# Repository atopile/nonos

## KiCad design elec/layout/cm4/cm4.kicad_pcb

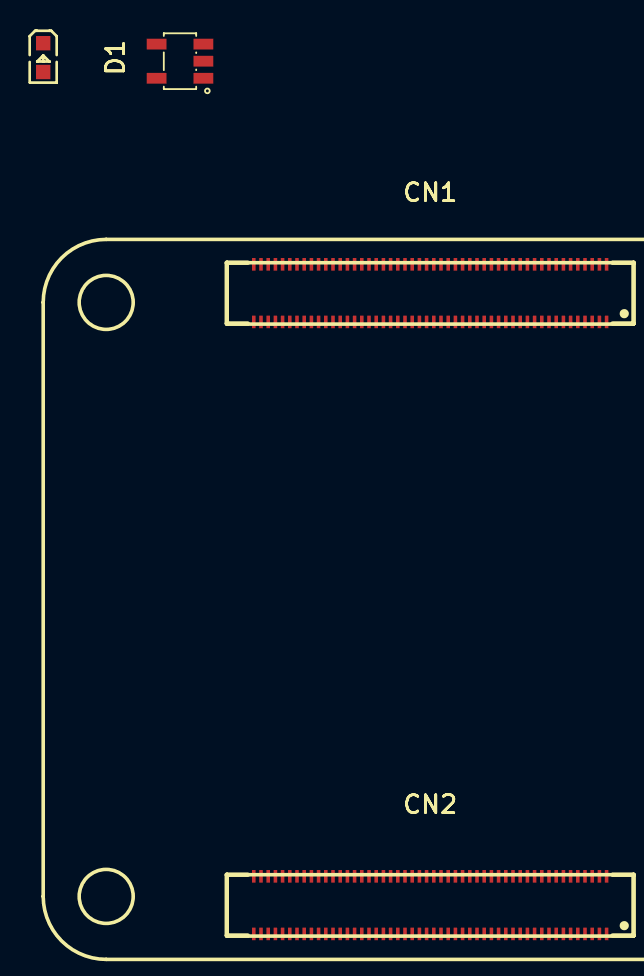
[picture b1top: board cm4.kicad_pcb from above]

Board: 2 copper layers, 4 parts (0 on the bottom side), 6 nets, no tracks yet.

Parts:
CN1, CN2: HRSHirose_DF40C_100DS_0_4V51; CONN-SMD_DF40C-100DS-0.4V-51
D1: 2.7V; LED0603-RD_WHITE
U1: _Texas_Instruments_SN74LVC1G07DBVR; SOT-23-5_L3.0-W1.7-P0.95-LS2.8-BR

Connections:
GND: CN1.1, CN1.4, CN1.7, CN1.11, CN1.16, CN1.21, CN1.26, CN1.30, CN1.33, CN1.37, CN1.49, CN1.65, CN1.68, CN1.71, CN1.74, CN1.79, CN1.84, CN1.89, CN1.90, CN1.94, CN1.97, CN1.100, CN2.4, CN2.7, CN2.10, CN2.13, CN2.16, CN2.19, CN2.22, CN2.28, CN2.31, CN2.34, CN2.37, CN2.40, CN2.43, CN2.46, CN2.49, CN2.52, CN2.55, CN2.58, CN2.61, CN2.64, CN2.67, CN2.70, CN2.73, CN2.82, CN2.85, CN2.88, CN2.91, CN2.94, CN2.97
PWR_LED: CN1.48, U1.2
VCC_1V8: CN1.44, CN1.45
VCC_3V3: CN1.39, CN1.42, CN1.43, D1.2, U1.5
VCC_5V: CN1.57, CN1.58, CN1.59, CN1.60, CN1.61, CN1.62
net: D1.1, U1.4

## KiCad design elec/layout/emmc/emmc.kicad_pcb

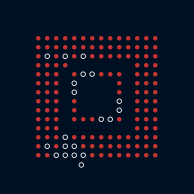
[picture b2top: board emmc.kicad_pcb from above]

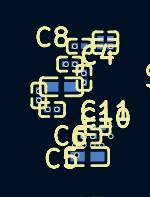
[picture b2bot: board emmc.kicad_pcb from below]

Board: 2 copper layers, 12 parts (11 on the bottom side), 5 nets, no tracks yet.

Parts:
C1: 10µF ±20% 6.3V X5R; C0402
C2, C3, C4, C6, C7, C8, C9, C11: 220nF ±20% 6.3V X5R; C0201
C5: 4.7µF ±20% 10V X5R; C0402
C10: 1µF ±20% 6.3V X5R; C0201
U1: _Samsung_KLMBG2JETD_B041; FBGA-153_L13.0-W11.5-P0.50_KLMAG1JETD-B041

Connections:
*6198-net: C5.1, C6.1, C7.1, C8.1, C9.1, U1.E6, U1.F5, U1.J10, U1.K9
*6198.eMMC.VDD_INTERNAL-net: C10.2, C11.2
VDD_INTERNAL: C10.1, C11.1, U1.C2
hv: C1.1, C2.1, C3.1, C4.1, U1.C6, U1.M4, U1.N4, U1.P3, U1.P5
lv: C1.2, C2.2, C3.2, C4.2, C5.2, C6.2, C7.2, C8.2, C9.2, U1.A6, U1.C4, U1.E7, U1.G5, U1.H10, U1.J5, U1.K8, U1.N2, U1.N5, U1.P4, U1.P6

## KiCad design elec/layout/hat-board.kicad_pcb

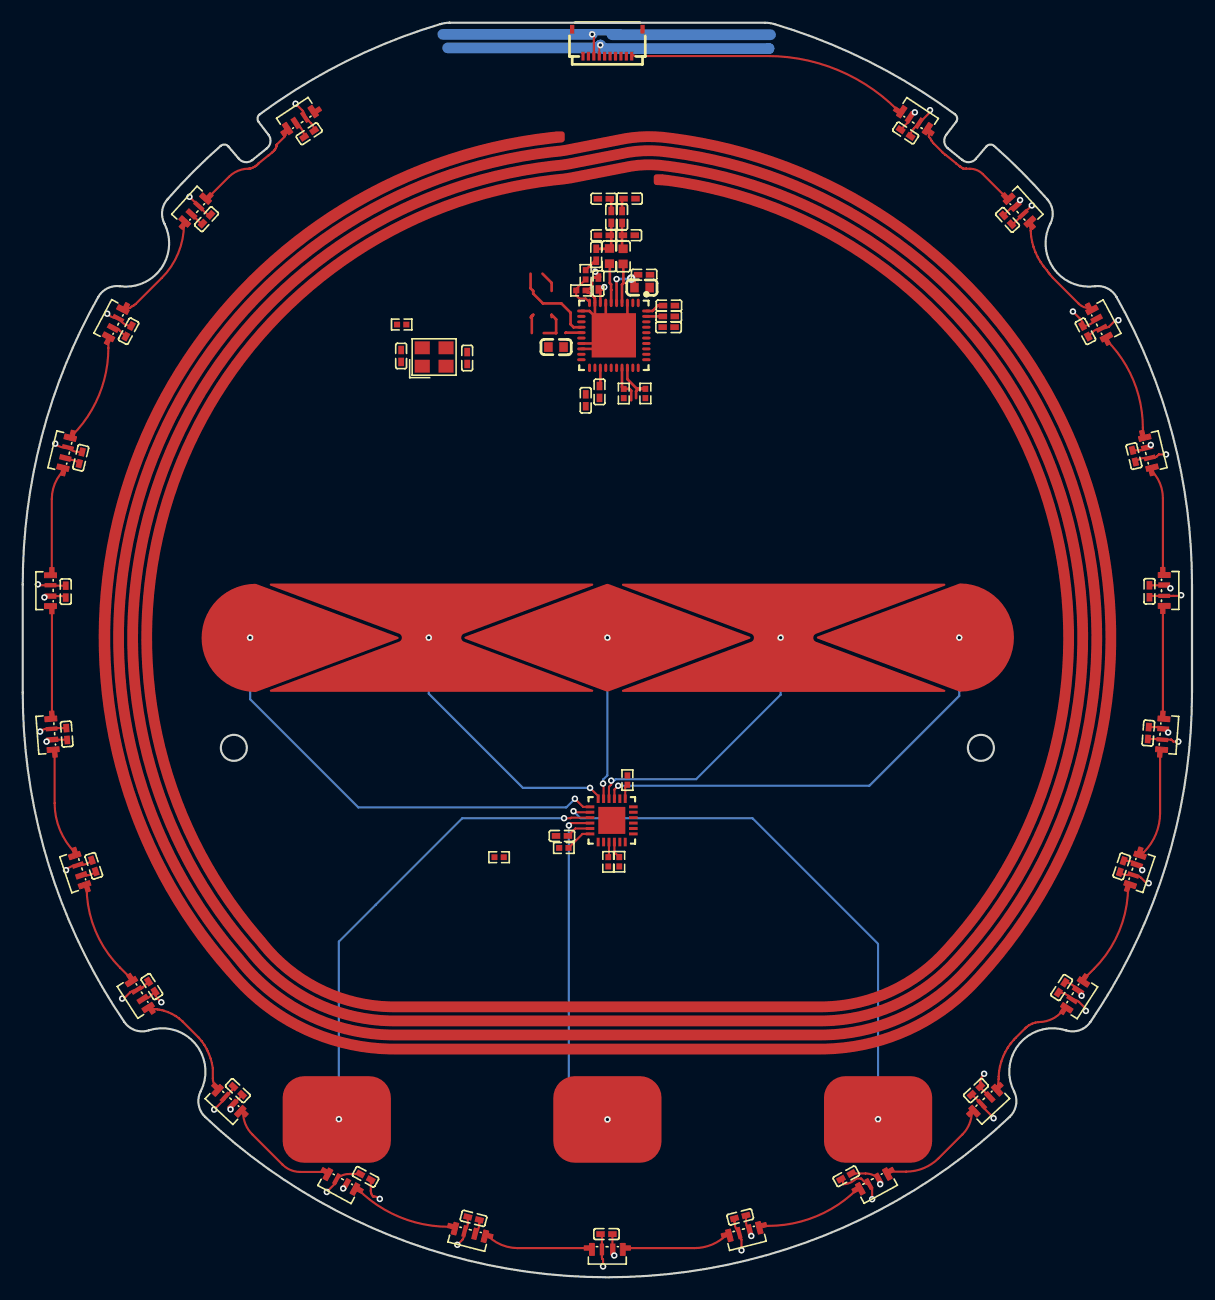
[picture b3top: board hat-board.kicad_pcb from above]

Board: 2 copper layers, 108.0 x 115.9 mm, 82 parts (0 on the bottom side), 60 nets.

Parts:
C1, C2, C14, C16: 20pF ±5% 50V C0G; C0402
C3, C5, C6, C7, C9, C10, C11, C12, C17, C18, C19, C20, C21, C22, C23, C24, C25, C26, C27, C28, C29, C30, C31, C32, C33, C34, C35, C36, C37, C38, C39, C42: 100nF ±10% 16V X7R; C0402
C4, C8: 10µF ±10% 10V X5R; C0603
C13, C15: 100pF ±5% 50V C0G; C0402
C40, C41: 220pF ±10% 50V X7R; C0402
FPC1: TE_Connectivity_1_2328702_0; FPC-SMD_10P-P0.50_HDGC_0.5K-HX-10PWB
L1, L2: 560nH ±5% 450mA 480mΩ; IND-SMD_L1.6-W0.8-1
P1: HatButtonAntenna; hat-button-antenna
R1, R2, R3, R5, R7, R8: 5.1kΩ ±1% 62.5mW; R0402
R4: 1kΩ ±1% 62.5mW; R0402
R6, R9, R10: 10kΩ ±1% 62.5mW; R0402
U1: _NXP_Semicon_PN5321A3HN_C106_51; QFN-40_L6.0-W6.0-P0.50-BL-EP4.1
U2, U3, U4, U5, U6, U7, U8, U9, U10, U11, U12, U13, U14, U15, U16, U17, U18, U19, U20, U21, U22, U23, U24: _OPSCO_Optoelectronics_SK6805SIDE_G_001; LED-SMD_4P-L3.5-W1.6_SK6805SIDE-G-001
U25: _Microchip_Tech_CAP1188_1_CP_TR; QFN-24_L4.0-W4.0-P0.50-TL-EP2.5
XTAL1: Crystal; CRYSTAL-SMD_4P-L3.2-W2.5-BL

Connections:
antenna_n: C15.1, C16.2, P1.9
antenna_p: C13.1, C14.2, P1.10
capacitive_sensor-net: R7.1, U25.4
capacitive_sensor-net-1: R8.1, U25.3
capacitive_sensor-net-2: R10.1, U25.24
capacitive_sensor-net-3: C42.2, U25.25
capacitive_sensor-net-4: C42.1, U25.23
capacitive_sensor.i2c-hv: R7.2, R8.2
gnd: C1.2, C2.2, C3.2, C4.2, C5.2, C6.2, C8.2, C9.2, C10.2, C11.1, C13.2, C15.2, C40.2, C41.2, FPC1.6, R5.1, U1.1, U1.3, U1.7, U1.9, U1.11, U1.17, U1.18, U1.41, XTAL1.2, XTAL1.4
hv: R1.2, R2.2
i2c_scl: FPC1.2, R1.1, U1.28
i2c_sda: FPC1.1, R2.1, U1.27
led_data: FPC1.10, U2.4
lv: C17.2, C18.2, C19.2, C20.2, C21.2, C22.2, C23.2, C24.2, C25.2, C26.2, C27.2, C28.2, C29.2, C30.2, C31.2, C32.2, C33.2, C34.2, C35.2, C36.2, C37.2, C38.2, C39.2, FPC1.3, U2.2, U3.2, U4.2, U5.2, U6.2, U7.2, U8.2, U9.2, U10.2, U11.2, U12.2, U13.2, U14.2, U15.2, U16.2, U17.2, U18.2, U19.2, U20.2, U21.2, U22.2, U23.2, U24.2
next_button: P1.3, U25.20
nfc-net: C12.2, R4.1
nfc-net-1: L1.2, U1.4
nfc-net-2: R4.2, R5.2, U1.10
nfc-net-3: R3.2, U1.15
nfc-net-4: C7.1, U1.37
nfc-net-5: C2.1, U1.14, XTAL1.3
nfc-net-6: L2.2, U1.6
nfc.nfc_ic-net: U1.20, U1.21, U1.22
nfc.oscillator-net: C1.1, R3.1, XTAL1.1
nfc_irq: FPC1.8, U1.25
play_button: P1.2, U25.22
power_3v3: C3.1, C4.1, C5.1, C6.1, C8.1, C9.1, C10.1, FPC1.5, U1.5, U1.8, U1.16, U1.23, U1.39, U1.40
power_5v: C17.1, C18.1, C19.1, C20.1, C21.1, C22.1, C23.1, C24.1, C25.1, C26.1, C27.1, C28.1, C29.1, C30.1, C31.1, C32.1, C33.1, C34.1, C35.1, C36.1, C37.1, C38.1, C39.1, FPC1.4, U2.3, U3.3, U4.3, U5.3, U6.3, U7.3, U8.3, U9.3, U10.3, U11.3, U12.3, U13.3, U14.3, U15.3, U16.3, U17.3, U18.3, U19.3, U20.3, U21.3, U22.3, U23.3, U24.3
prev_button: P1.1, U25.21
reset: FPC1.7, U1.26
signal: U3.4, U24.1
signal-1: U23.1, U24.4
signal-2: U9.1, U10.4
signal-3: U8.1, U9.4
signal-4: U3.1, U4.4
signal-5: U15.1, U16.4
signal-6: U21.1, U22.4
signal-7: U20.1, U21.4
signal-8: U19.1, U20.4
signal-9: U18.1, U19.4
signal-10: U10.1, U11.4
signal-11: U7.1, U8.4
signal-12: U6.1, U7.4
signal-13: U13.1, U17.4
signal-14: U2.1, U13.4
signal-15: U12.1, U14.4
signal-16: U11.1, U12.4
signal-17: U17.1, U18.4
signal-18: U4.1, U5.4
signal-19: U5.1, U6.4
signal-20: U22.1, U23.4
signal-21: U14.1, U15.4
slider_0: P1.4, U25.19
slider_1: P1.5, U25.18
slider_2: P1.6, U25.17
slider_3: P1.7, U25.16
slider_4: P1.8, U25.15
touch_irq: FPC1.9, R9.1, U25.13
tx_1_mid: C14.1, C40.1, L1.1
tx_2_mid: C12.1, C16.1, C41.1, L2.1

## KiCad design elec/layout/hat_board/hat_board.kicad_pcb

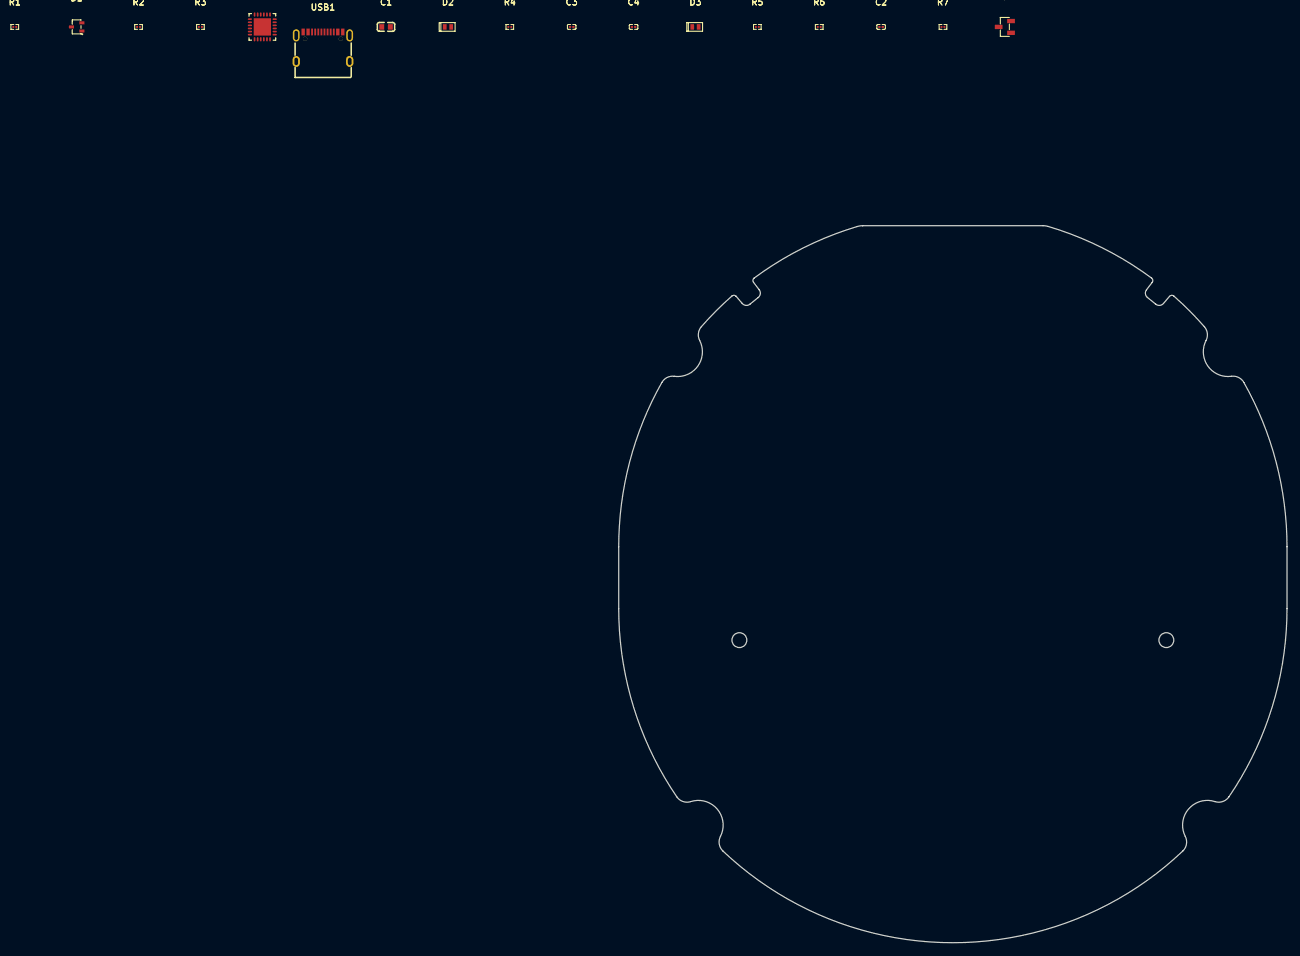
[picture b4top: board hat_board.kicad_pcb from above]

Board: 2 copper layers, 108.0 x 115.9 mm, 17 parts (0 on the bottom side), 17 nets, no tracks yet.

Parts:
C1: 4.7µF ±10% 35V X5R; C0603
C2: 100nF ±10% 10V X5R; C0201
C3: C0201
C4: 1µF ±20% 6.3V X5R; C0201
D1: ESDA25W; SOT-323-3_L2.1-W1.3-P1.32-LS2.1-BR
D2, D3: DFN1610-2_L1.6-W1.0-P1.05-RD
Q1: MOSFET; SOT-23-3_L2.9-W1.3-P1.90-LS2.4-BR
R1: 1kΩ ±1% 50mW; R0201
R2: 4.64kΩ ±1% 50mW; R0201
R3, R4: R0201
R5: 100kΩ ±1% 50mW; R0201
R6: 22.1kΩ ±1% 50mW; R0201
R7: 100Ω ±1% 50mW; R0201
U1: STUSB4500QTR; QFN-24_L4.0-W4.0-P0.50-BL-EP2.8
USB1: TYPE_C_16PIN_2MD073; USB-C-SMD_TYPE-C-6PIN-2MD-073

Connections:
CC1: D1.1, U1.1, U1.2, USB1.4
CC2: D1.2, U1.4, U1.5, USB1.10
I2C_SCL: R2.1, U1.7
I2C_SDA: R3.1, U1.8
USB_CONNECTOR-net: USB1.5, USB1.7
USB_CONNECTOR-net-1: USB1.6, USB1.8
VBUS: C1.2, C2.2, D2.1, Q1.2, R1.1, R4.1, U1.24, USB1.2, USB1.11
VREG_1V2: C3.2, U1.21
VREG_2V7: C4.2, U1.23
VSINK_VCC: D3.1, Q1.3, R5.2
hv: R2.2, R3.2
lv: C1.1, C3.1, C4.1, D1.3, D2.2, D3.2, U1.6, U1.10, U1.12, U1.13, U1.22, U1.25, USB1.1, USB1.12, USB1.13, USB1.14
net: Q1.1, R5.1, R6.1, R7.1
net-1: R6.2, U1.16
net-2: R1.2, U1.9
net-3: R4.2, U1.18
net-4: C2.1, R7.2

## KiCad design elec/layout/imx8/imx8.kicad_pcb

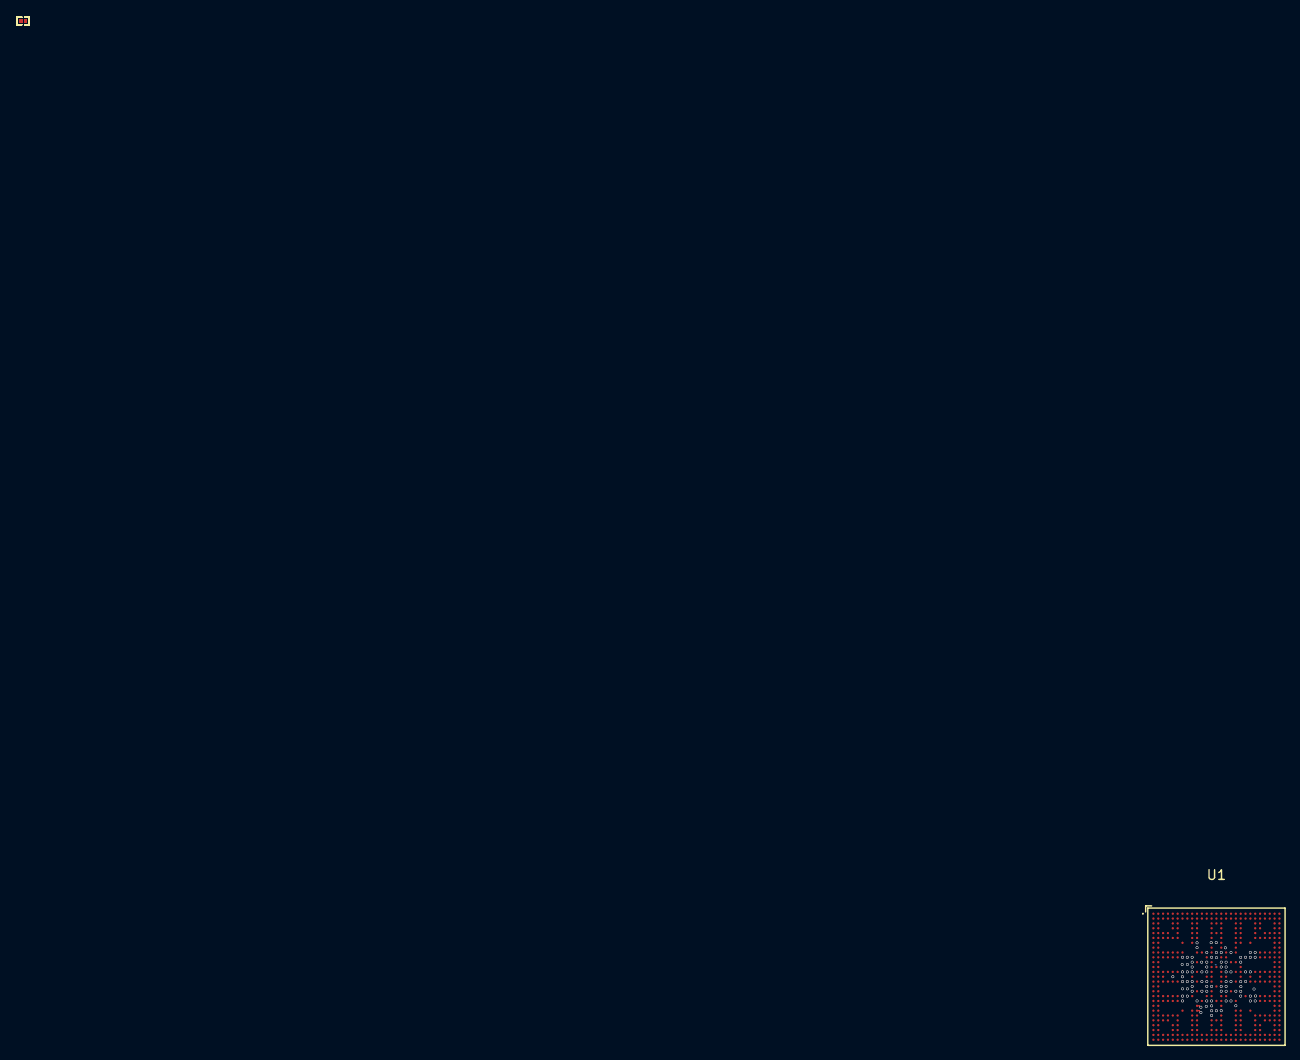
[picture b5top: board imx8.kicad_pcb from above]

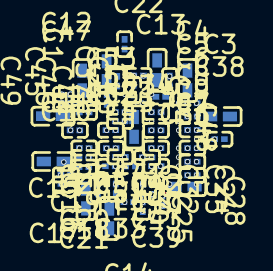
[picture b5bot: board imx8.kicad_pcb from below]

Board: 2 copper layers, 68 parts (55 on the bottom side), 28 nets.

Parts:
C1: 2.2µF ±20% 6.3V X5R; C0201
C2, C3, C15, C17, C30, C36, C37, C48: 10µF ±20% 6.3V X5R; C0402
C4, C5, C6, C7, C8, C9, C12, C14, C31, C32, C33, C34, C35, C38, C39, C40, C41, C42, C43, C50, C51, C52, C53, C54: 1µF ±20% 6.3V X5R; C0201
C10, C11, C13, C16, C18, C19, C20, C21, C22, C23, C24, C26, C27, C28, C29, C44, C46, C47, C55: 220nF ±20% 6.3V X5R; C0201
C25, C49: 4.7µF ±20% 10V X5R; C0402
C45: 2.2µF ±20% 6.3V X5R; C0402
R1: 10kΩ ±1% 50mW; R0201
R2, R3, R4, R5, R6, R7, R8, R9: 4.87kΩ ±1% 50mW; R0201
R10, R11, R12: 100kΩ ±1% 50mW; R0201
U1: _NXP_Semicon_MIMX8MM6CVTKZAA; BGA-486_L14.0-W14.0-P0.50-TL_NXP_MIMX8MMXDVTLZXA

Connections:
*A7C8-hv: C12.1, R10.2, R11.2, R12.2, U1.J22
*A7C8-net-0: C48.1, C49.1, C50.1, C51.1, C52.1, C53.1, C54.1, C55.1, U1.J16, U1.J17, U1.K15, U1.K16, U1.L15, U1.L17, U1.L18, U1.M15, U1.N13, U1.N15, U1.N17, U1.N18, U1.P16, U1.R17, U1.R18, U1.U17, U1.U18
*A7C8-net-1: C36.1, C37.1, C38.1, C39.1, C40.1, C41.1, C42.1, C43.1, U1.J10, U1.K12, U1.K13, U1.L10, U1.L11, U1.L13, U1.M13, U1.M14, U1.N10, U1.N11, U1.P5, U1.P12, U1.R10, U1.R11, U1.U10, U1.U11, U1.V12, U1.W10, U1.W11
*A7C8-net-2: R6.1, U1.E10
*A7C8-net-3: C30.1, C31.1, C32.1, C33.1, C34.1, C35.1, U1.R13, U1.R15, U1.T13, U1.T14, U1.T15, U1.U13, U1.U15, U1.V13, U1.V15, U1.V16, U1.W13, U1.W14, U1.W15, U1.W16
*A7C8-net-4: R9.1, U1.E13
*A7C8-net-5: C25.1, C26.1, C27.1, C28.1, C29.1, U1.H10, U1.K19, U1.W17, U1.W18, U1.Y10
*A7C8-net-6: C44.1, U1.J14
*A7C8-net-7: C10.1, U1.W22
*A7C8-net-8: C45.1, C46.1, U1.J15
*A7C8-net-9: R4.1, U1.D10
*A7C8-net-10: C13.1, C14.1, U1.N19, U1.R19
*A7C8-net-11: R1.1, U1.R1
*A7C8-net-12: R8.1, U1.D13
*A7C8-net-13: C1.1, U1.D15
*A7C8-net-14: R2.1, U1.E9
*A7C8-net-15: R7.1, U1.F10
*A7C8-net-16: R3.1, U1.F9
*A7C8-net-17: C11.1, U1.V22
*A7C8-net-18: R5.1, U1.D9
*A7C8.I2C1-hv: R2.2, R3.2
*A7C8.I2C2-hv: R4.2, R5.2
*A7C8.I2C3-hv: R6.2, R7.2
*A7C8.I2C4-hv: R8.2, R9.2
hv: C2.1, C3.1, C4.1, C5.1, C6.1, C7.1, C8.1, C9.1, U1.K8, U1.K9, U1.L9, U1.M9, U1.N8, U1.N9, U1.P7, U1.R8, U1.R9, U1.T9, U1.U9, U1.V8, U1.V9
lv: C1.2, C2.2, C3.2, C4.2, C5.2, C6.2, C7.2, C8.2, C9.2, C10.2, C11.2, C12.2, C13.2, C14.2, C15.2, C16.2, C17.2, C18.2, C19.2, C20.2, C21.2, C22.2, C23.2, C24.2, C25.2, C26.2, C27.2, C28.2, C29.2, C30.2, C31.2, C32.2, C33.2, C34.2, C35.2, C36.2, C37.2, C38.2, C39.2, C40.2, C41.2, C42.2, C43.2, C44.2, C45.2, C46.2, C47.2, C48.2, C49.2, C50.2, C51.2, C52.2, C53.2, C54.2, C55.2, R1.2, U1.A1, U1.A27, U1.AA7, U1.AA9, U1.AA10, U1.AA13, U1.AA15, U1.AA18, U1.AA19, U1.AA21, U1.AB3, U1.AB25, U1.AC3, U1.AC25, U1.AE2, U1.AE5, U1.AE6, U1.AE9, U1.AE10, U1.AE13, U1.AE14, U1.AE15, U1.AE18, U1.AE19, U1.AE22, U1.AE23, U1.AF3, U1.AG1, U1.AG27, U1.B3, U1.B26, U1.C2, U1.C5, U1.C6, U1.C9, U1.C10, U1.C13, U1.C14, U1.C15, U1.C18, U1.C19, U1.C22, U1.C23, U1.E3, U1.E25, U1.F3, U1.F25, U1.G7, U1.G9, U1.G10, U1.G13, U1.G15, U1.G18, U1.G19, U1.G21, U1.H2, U1.H18, U1.J3, U1.J7, U1.J21, U1.J25, U1.K3, U1.K7, U1.K20, U1.K21, U1.K25, U1.L12, U1.L16, U1.M12, U1.M16, U1.N3, U1.N7, U1.N12, U1.N16, U1.N21, U1.N25, U1.P3, U1.P13, U1.P15, U1.P21, U1.P25, U1.R3, U1.R7, U1.R12, U1.R16, U1.R20, U1.R21, U1.R25, U1.T12, U1.T16, U1.U12, U1.U16, U1.V3, U1.V7, U1.V21, U1.V25, U1.W3, U1.W7, U1.W21, U1.W25, U1.Y2, U1.Y13, U1.Y18
net-0: C15.1, C16.1, C17.1, C18.1, C19.1, C20.1, C21.1, C22.1, C23.1, C24.1, U1.AA14, U1.AB13, U1.G14, U1.H13, U1.H15, U1.J11, U1.J12, U1.J13, U1.L19, U1.M19, U1.N20, U1.P19, U1.T19, U1.U19, U1.V19, U1.V20, U1.W12, U1.Y15
net-1: C47.1, U1.K22
